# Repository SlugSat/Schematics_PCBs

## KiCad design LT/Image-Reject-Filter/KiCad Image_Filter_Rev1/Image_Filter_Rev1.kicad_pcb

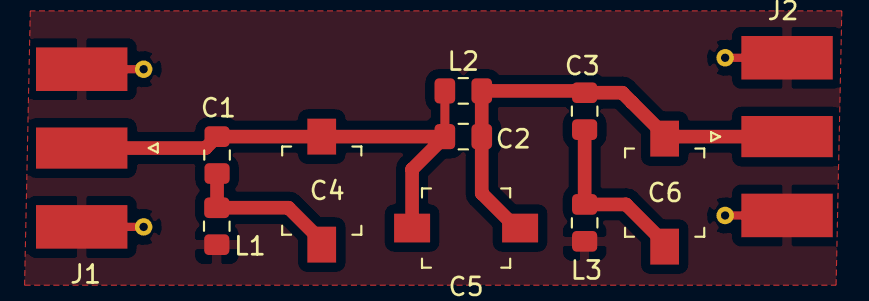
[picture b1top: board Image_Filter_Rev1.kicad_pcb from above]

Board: 2 copper layers, 11 parts (0 on the bottom side), 5 nets.

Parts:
C1, C3: 27pF; C_0805_2012Metric_Pad1.15x1.40mm_HandSolder
C2: 180pF; C_0805_2012Metric_Pad1.15x1.40mm_HandSolder
C4, C5, C6: C_Variable; C_Trimmer_Murata_TZB4-B
J1, J2: Conn_Coaxial; SMA_Molex_73251-1153_EdgeMount_Horizontal
L1, L3: 510nH; L_0805_2012Metric_Pad1.15x1.40mm_HandSolder
L2: 75nH; L_0805_2012Metric_Pad1.15x1.40mm_HandSolder

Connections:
GND: J1.2, J2.2, L1.2, L3.2
unnamed: C1.1, C2.2, C4.1, C5.2, J1.1, L2.1
unnamed: C1.2, C4.2, L1.1
unnamed: C2.1, C3.1, C5.1, C6.1, J2.1, L2.2
unnamed: C3.2, C6.2, L3.1

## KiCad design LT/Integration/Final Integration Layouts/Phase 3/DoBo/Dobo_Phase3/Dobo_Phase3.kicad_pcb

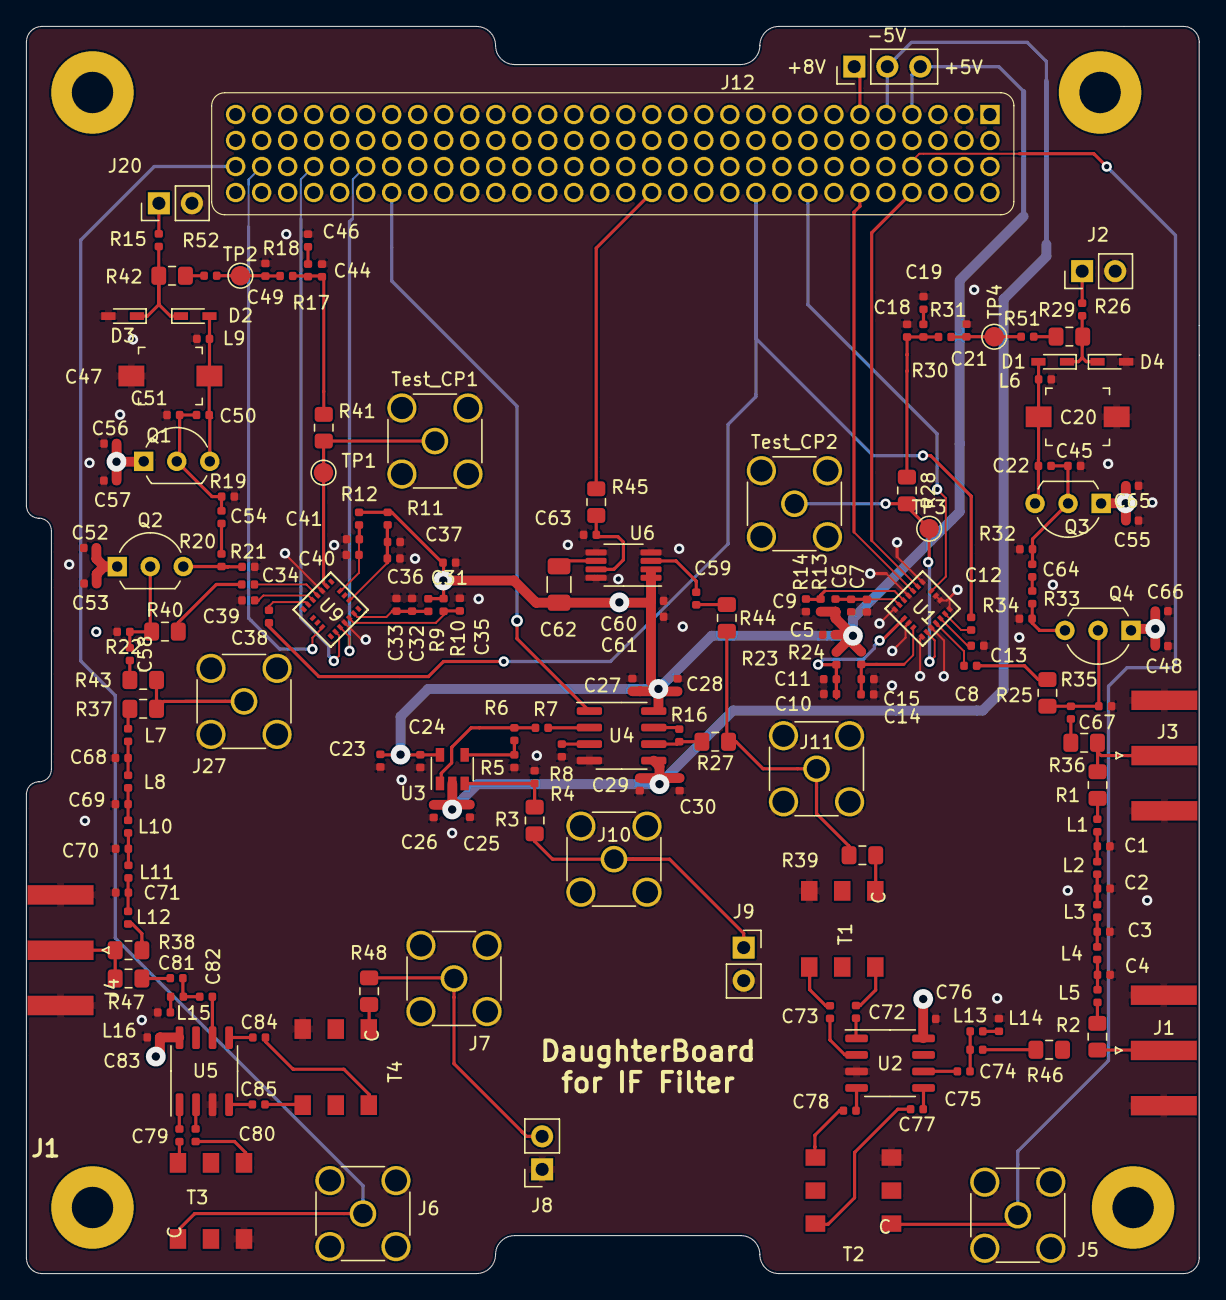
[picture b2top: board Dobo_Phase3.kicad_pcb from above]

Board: 4 copper layers, 90.2 x 95.9 mm, 187 parts (0 on the bottom side), 113 nets.

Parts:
C1: 91pF; C_0402_1005Metric
C2, C3, C4: 160pF; C_0402_1005Metric
C5, C6, C9, C10, C13, C14, C31, C32, C35, C36, C39, C40, C53, C55, C57, C58, C66, C67: 100nF; C_0402_1005Metric
C7, C11, C15, C33, C37, C41, C48, C52, C56, C61, C63, C65: 100pF; C_0402_1005Metric
C8, C12, C34, C38: 1000pF; C_0402_1005Metric
C18, C44: 12nF; C_0402_1005Metric
C19, C46: 80nF; C_0402_1005Metric
C20, C47: SGC35060; C_Trimmer_Murata_TZB4-B
C21, C49: 220nF; C_0402_1005Metric
C22, C50: 22pF; C_0402_1005Metric
C23, C25: 4.7uF; C_0402_1005Metric
C24, C26: 10nF; C_0402_1005Metric
C27, C29, C59, C60: 0.1uH; C_0402_1005Metric
C28, C30: 6.8uH; C_0402_1005Metric
C45, C51: 47pF; C_0402_1005Metric
C54, C64: 10pF; C_0402_1005Metric
C62: 100uH; C_1206_3216Metric
C68, C71: 120pF; C_0402_1005Metric
C69, C70: 200pF; C_0402_1005Metric
C72, C73, C75, C76, C77, C78, C79, C80, C82, C83, C84, C85: 10u; C_0402_1005Metric
C74, C81: 2.2n; C_0402_1005Metric
D1, D2, D3, D4: 1SV304; D_SC-80_HandSoldering
J1, J3, J4: Conn_Coaxial; SMA_Amphenol_132289_EdgeMount
J2, J20: Conn_01x02_Male; PinHeader_1x02_P2.54mm_Vertical
J5, J6, J7, J10, J11, J27: Conn_Coaxial; SMA_Amphenol_132291_Vertical
J8, J9: Conn_01x02_Female; PinSocket_1x02_P2.54mm_Vertical
J12: Conn_01x03_Male; PinHeader_1x03_P2.54mm_Vertical
J46: Bus; STD_PCB_A1_v1.1
L1, L5: shorted; L_0402_1005Metric
L2, L4: 270nH; L_0402_1005Metric
L3: 330nH; L_0402_1005Metric
L6, L9: 680nH; L_0402_1005Metric
L7, L12: Matching; L_0402_1005Metric
L8: 360nH; L_0402_1005Metric
L10: 390pF; L_0402_1005Metric
L11: 360pF; L_0402_1005Metric
L13, L15: 5.6u; L_0402_1005Metric
L14, L16: 680n; L_0402_1005Metric
Q1, Q2, Q3, Q4: 2N5486 JFET; TO-92L_Inline_Wide
R1, R2, R3, R25, R27, R28, R29, R36, R37, R38, R39, R40, R41, R42, R43, R44, R45, R46, R47, R48: 0; R_0805_2012Metric_Pad1.15x1.40mm_HandSolder
R4, R5: 50; R_0402_1005Metric
R6, R16: 1000; R_0402_1005Metric
R7, R8: 29.4; R_0402_1005Metric
R9, R11, R12, R13, R23, R24: 18; R_0402_1005Metric
R10, R14, R15, R26, R51, R52: 10k; R_0402_1005Metric
R17, R30: 62k; R_0402_1005Metric
R18, R19, R22, R31, R32, R35: 1k; R_0402_1005Metric
R20, R33: 1 Ohm; R_0402_1005Metric
R21, R34: 100k; R_0402_1005Metric
T1, T2, T3, T4: Transformer_6; PWB1040L
TP1, TP2, TP3, TP4: TestPoint; TestPoint_Pad_D1.5mm
Test_CP1, Test_CP2: Conn_Coaxial; SMA_Amphenol_132291_Vertical
U1, U9: LMX231X
U2, U5: SA602; SO-8_3.9x4.9mm_P1.27mm
U3: LMH6624; SOT-23-5
U4: LMH6505; SOIC-8_3.9x4.9mm_P1.27mm
U6: AD8361; MSOP-8_3x3mm_P0.65mm

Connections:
+5V: C5.2, C23.1, C24.1, C27.2, C28.2, C31.2, C60.1, C61.1, C62.2, J12.3, J46.4, R9.1, R10.1, R11.1, R12.1, R13.1, R14.1, R23.1, R24.1, U3.5, U4.8, U6.1, U6.2
+8V: C48.2, C52.2, C53.2, C55.2, C56.2, C57.2, C65.2, C66.2, C76.1, C83.1, J12.1, J46.6, Q1.1, Q2.1, Q3.1, Q4.1, U2.8, U5.8
-5V: C25.2, C26.2, C29.2, C30.2, J12.2, J46.5, U3.2, U4.5
/Down_Mixer-IF_Filter: J7.1, J8.2, R48.1
/IF_Filter-VGA: J9.1, J10.1, R3.2
/LPF-Down_Mixer: J4.1, R38.1, R47.2
/Low Pass Filter for 10m PLL/Local_Oscillator_Output: J1.1, R2.1
/PLL_10m_LPF: J3.1, R1.2, R36.1
/PLL_15m-LPF: J27.1, R37.2, R43.1
/VGA-Detector: J11.1, R27.1, R39.2, R44.2
Bus_64: J5.1, J46.64, T2.1
Bus_85: J46.85, U9.13
Bus_87: J46.87, U9.12
Bus_89: J46.89, U9.10
Bus_90: J6.1, J46.90, T3.1
Bus_94: J46.94, U1.12
Bus_96: J46.96, U1.13
Bus_99: J46.98, U1.10
Bus_100: C12.1, C38.1, J46.100
Bus_104: J46.104, R45.1
Bus_114: J46.114, U4.1
CE: C35.2, R10.2, U9.15
CE_2: C9.2, R14.2, U1.15
CPo: R41.2, TP1.1, Test_CP1.1, U9.2
CPo_2: R28.2, TP3.1, Test_CP2.1, U1.2
F_IN: C34.2, U9.4
F_IN_2: C8.2, U1.4
GND: C1.2, C2.2, C3.2, C4.2, C5.1, C6.1, C7.1, C9.1, C10.1, C11.1, C13.1, C14.1, C15.1, C18.1, C19.2, C20.2, C21.2, C23.2, C24.2, C25.1, C26.1, C27.1, C28.1, C29.1, C30.1, C31.1, C32.1, C33.1, C35.1, C36.1, C37.1, C39.1, C40.1, C41.1, C44.1, C45.1, C46.2, C47.2, C48.1, C49.2, C51.1, C52.1, C53.1, C55.1, C56.1, C57.1, C60.2, C61.2, C63.2, C65.1, C66.1, C68.2, C69.2, C70.2, C71.2, C76.2, C83.2, D3.2, D4.2, J1.2, J2.2, J3.2, J4.2, J5.2, J6.2, J7.2, J8.1, J9.2, J10.2, J11.2, J20.2, J27.2, J46.2, L6.2, L9.2, L14.2, L16.2, R4.1, R5.2, R8.2, R19.2, R21.2, R22.2, R32.2, R34.2, R35.2, T1.3, T2.3, T3.3, T4.3, Test_CP1.2, Test_CP2.2, U1.1, U1.3, U1.7, U1.8, U1.9, U1.11, U1.14, U1.17, U1.19, U2.3, U4.4, U5.3, U6.4, U6.5, U6.8, U9.3, U9.14
unnamed: C1.1, L1.2, L2.1
unnamed: C2.1, L2.2, L3.1
unnamed: C3.1, L3.2, L4.1
unnamed: C4.1, L4.2, L5.1
unnamed: C8.1, R25.2
unnamed: C12.2, U1.6
unnamed: C13.2, U1.5
unnamed: C18.2, R28.1, R30.2, R31.2
unnamed: C19.1, R30.1
unnamed: C20.1, C22.2, D1.2, L6.1, Q3.3
unnamed: C21.1, R31.1, R51.1, TP4.1
unnamed: C22.1, C45.2, C64.1, Q3.2, R32.1
unnamed: C34.1, R40.2
unnamed: C38.2, U9.6
unnamed: C39.2, U9.5
unnamed: C44.2, R17.2, R18.2, R41.1
unnamed: C46.1, R17.1
unnamed: C47.1, C50.2, D2.2, L9.1, Q1.3
unnamed: C49.1, R18.1, R52.1, TP2.1
unnamed: C50.1, C51.2, C54.1, Q1.2, R19.1
unnamed: C54.2, R20.2
unnamed: C58.1, Q2.2, R22.1, R40.1
unnamed: C58.2, R43.2
unnamed: C59.1, U6.3
unnamed: C59.2, R44.1
unnamed: C62.1, U6.6
unnamed: C63.1, R45.2, U6.7
unnamed: C64.2, R33.2
unnamed: C67.1, Q4.2, R25.1, R35.1
unnamed: C67.2, R36.2
unnamed: C68.1, L7.2, L8.1
unnamed: C69.1, L8.2, L10.1
unnamed: C70.1, L10.2, L11.1
unnamed: C71.1, L11.2, L12.1
unnamed: C72.1, U2.1
unnamed: C72.2, T1.6
unnamed: C73.1, U2.2
unnamed: C73.2, T1.4
unnamed: C74.1, R46.1
unnamed: C74.2, C75.1, L13.1
unnamed: C75.2, U2.6
unnamed: C77.1, U2.5
unnamed: C77.2, T2.6
unnamed: C78.1, U2.4
unnamed: C78.2, T2.4
unnamed: C79.1, U5.1
unnamed: C79.2, T3.6
unnamed: C80.1, U5.2
unnamed: C80.2, T3.4
unnamed: C81.1, R47.1
unnamed: C81.2, C82.1, L15.1
unnamed: C82.2, U5.6
unnamed: C84.1, U5.5
unnamed: C84.2, T4.6
unnamed: C85.1, U5.4
unnamed: C85.2, T4.4
unnamed: D1.1, D4.1, R26.2, R29.2
unnamed: D2.1, D3.1, R15.2, R42.2
unnamed: J2.1, R26.1
unnamed: J20.1, R15.1
unnamed: L1.1, R1.1
unnamed: L5.2, R2.2
unnamed: L7.1, R37.1
unnamed: L12.2, R38.2
unnamed: L13.2, L14.1
unnamed: L15.2, L16.1
unnamed: Q2.3, R20.1, R21.1
unnamed: Q4.3, R33.1, R34.1
unnamed: R3.1, R4.2, U3.3
unnamed: R5.1, R6.2, U3.4
unnamed: R6.1, R7.2, U3.1
unnamed: R7.1, U4.2
unnamed: R8.1, U4.3
unnamed: R16.1, R27.2, U4.6
unnamed: R16.2, U4.7
unnamed: R29.1, R51.2
unnamed: R39.1, T1.1
unnamed: R42.1, R52.2
unnamed: R48.2, T4.1
V_uC: C32.2, C33.2, R9.2, U9.16
V_uC_2: C6.2, C7.2, R13.2, U1.16
Vcc: C36.2, C37.2, R11.2, U9.18
Vcc_2: C10.2, C11.2, R23.2, U1.18
Vp: C40.2, C41.2, R12.2, U9.20
Vp_2: C14.2, C15.2, R24.2, U1.20

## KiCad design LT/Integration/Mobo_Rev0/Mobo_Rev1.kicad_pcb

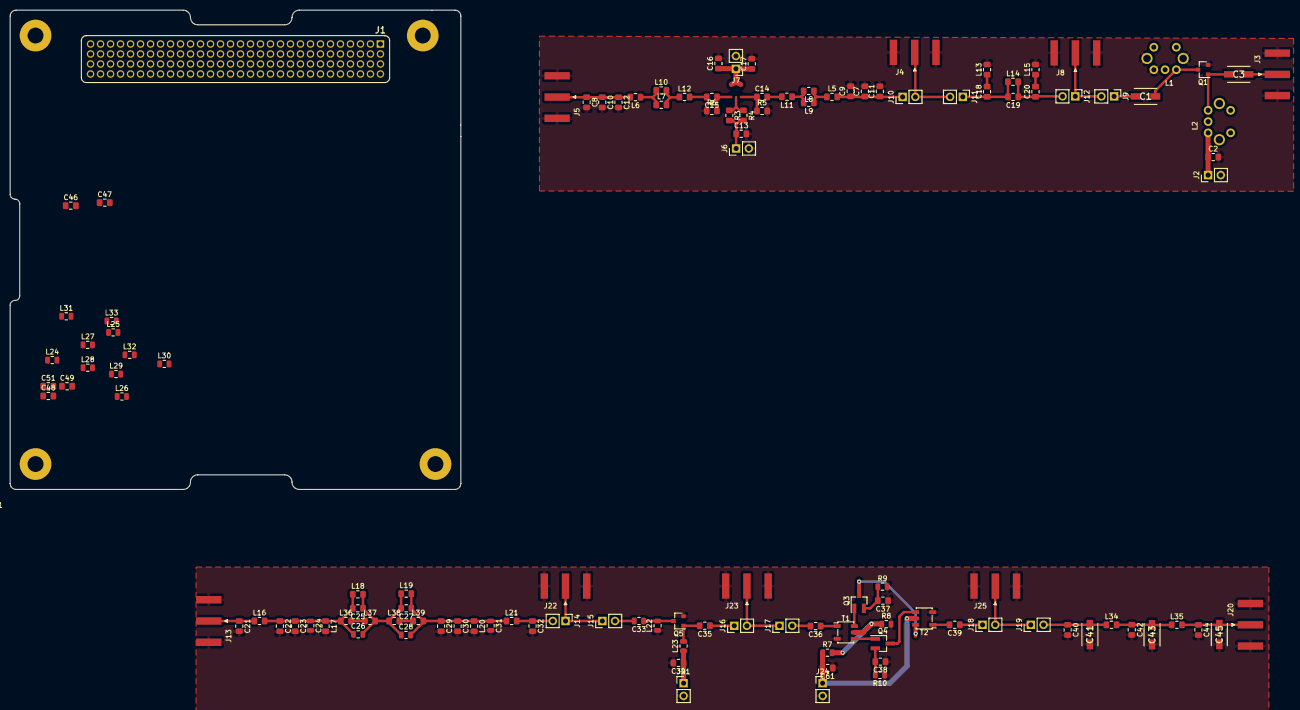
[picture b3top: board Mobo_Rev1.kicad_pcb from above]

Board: 2 copper layers, 90.2 x 95.9 mm, 124 parts (0 on the bottom side), 54 nets.

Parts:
C1, C3: 8-30pF; CAP_trimmer_SGC3_Download
C2, C34: 1uF; C_0805_2012Metric_Pad1.15x1.40mm_HandSolder
C7, C8: 220pF; C_0805_2012Metric_Pad1.15x1.40mm_HandSolder
C9, C10: 22pF; C_0805_2012Metric_Pad1.15x1.40mm_HandSolder
C11, C12: 330pF; C_0805_2012Metric_Pad1.15x1.40mm_HandSolder
C13: 10nH; C_0805_2012Metric_Pad1.15x1.40mm_HandSolder
C14, C15, C16, C17: 10nF; C_0805_2012Metric_Pad1.15x1.40mm_HandSolder
C18, C20: 27pF; C_0805_2012Metric_Pad1.15x1.40mm_HandSolder
C19: 180pF; C_0805_2012Metric_Pad1.15x1.40mm_HandSolder
C21, C32: No Connect; C_0805_2012Metric_Pad1.15x1.40mm_HandSolder
C22: 560p; C_0805_2012Metric_Pad1.15x1.40mm_HandSolder
C23, C30: 56pF; C_0805_2012Metric_Pad1.15x1.40mm_HandSolder
C24, C26, C28, C31: No Connect; C_0805_2012Metric
C25: 18pF; C_0805_2012Metric_Pad1.15x1.40mm_HandSolder
C27: 43pF; C_0805_2012Metric_Pad1.15x1.40mm_HandSolder
C29: 560pF; C_0805_2012Metric_Pad1.15x1.40mm_HandSolder
C33: C_Variable; C_0805_2012Metric
C35, C36, C39, C46, C47, C48, C49, C51: C; C_0805_2012Metric_Pad1.15x1.40mm_HandSolder
C37, C38, C61: 100n; C_0805_2012Metric_Pad1.15x1.40mm_HandSolder
C40, C44: 180p; C_0805_2012Metric_Pad1.15x1.40mm_HandSolder
C41, C43, C45: C_Variable; CAP_trimmer_SGC3_Download
C42: 270p; C_0805_2012Metric_Pad1.15x1.40mm_HandSolder
J1: Bus; STD_PCB_A1_v1.1
J2, J6, J7, J9, J10, J11, J12, J14, J15, J16, J17, J18, J19, J21, J24: Conn_01x02_Male; PinHeader_1x02_P2.54mm_Vertical
J3, J4, J5, J8, J13, J20: Conn_Coaxial; SMA_Amphenol_132289_EdgeMount
J22, J23, J25: Conn_01x02_Male; SMA_Amphenol_132289_EdgeMount
L1: 0.54-0.81uH; IND_trimmer_7M3
L2: 1.8-2.6uH; IND_trimmer_7M3
L5, L6: 3.9nH; L_0805_2012Metric_Pad1.15x1.40mm_HandSolder
L7, L8, L9, L10, L17, L20: 47nH; L_0805_2012Metric_Pad1.15x1.40mm_HandSolder
L11, L12: 150nH; L_0805_2012Metric_Pad1.15x1.40mm_HandSolder
L13, L15: 470nH; L_0805_2012Metric_Pad1.15x1.40mm_HandSolder
L14: 82nH; L_0805_2012Metric_Pad1.15x1.40mm_HandSolder
L16, L21: Shorted Connection; L_0805_2012Metric_Pad1.15x1.40mm_HandSolder
L18, L19: No Connect; L_0805_2012Metric_Pad1.15x1.40mm_HandSolder
L22: LTRIM; L_0805_2012Metric
L23: 1.8-2.6uH; L_0805_2012Metric
L24, L25, L26, L27, L28, L29, L30, L31, L32, L33: L; L_0805_2012Metric
L34, L35: 330n; L_0805_2012Metric_Pad1.15x1.40mm_HandSolder
L36: 680nH; L_0805_2012Metric_Pad1.15x1.40mm_HandSolder
L37: 6.8nH; L_0805_2012Metric_Pad1.15x1.40mm_HandSolder
L38: 1.5uH; L_0805_2012Metric_Pad1.15x1.40mm_HandSolder
L39: 72nH; L_0805_2012Metric_Pad1.15x1.40mm_HandSolder
Q1: 2N5486; SOT-23
Q3: Q_NPN_BEC; SOT-23_Handsoldering
Q4: Q_PNP_BEC; SOT-23_Handsoldering
Q5: Q_NJFET_DSG; SOT-23
R3, R4: 120; R_0805_2012Metric_Pad1.15x1.40mm_HandSolder
R5, R6: 330; R_0805_2012Metric_Pad1.15x1.40mm_HandSolder
R7: 33k; C_0805_2012Metric
R8: 47k; C_0805_2012Metric
R9, R10: 470; C_0805_2012Metric
T1, T2: TC2-1T+; Transformer_MACOM_SM-22

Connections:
+5V: C16.1, C17.1, J7.1
+8V: C2.1, C34.1, J2.1, J21.1, L2.1, L23.1
/29.4 MHz Bandpass Filter/29.4BPF_OUT: J14.1, J22.1
/Image Reject Filter/Image_Reject_Out: J8.1, J12.1
/LNA/LNAout: C3.1, J3.1
/Power Amplifier/PA_OUT: J18.2, J25.1
/Pre Amplifier/PREAMP_OUT: J16.2, J23.1
/Variable Attenuator/Variable_Attenuator_Out: J4.1, J10.2
GND: C2.2, C7.2, C8.2, C9.2, C10.2, C11.2, C12.2, C13.2, C16.2, C17.2, C21.2, C22.2, C23.2, C24.2, C29.2, C30.2, C31.2, C32.2, C34.2, C37.1, C38.1, C40.2, C41.2, C42.2, C43.2, C44.2, C45.2, C61.1, J2.2, J3.2, J4.2, J5.2, J6.2, J7.2, J8.2, J13.2, J20.2, J21.2, J22.2, J23.2, J24.2, J25.2, L1.2, L13.2, L15.2, L17.2, L20.2, L22.1, Q1.3, Q5.2, R5.2, R6.1, R8.2, R9.2, R10.1, T1.2, T2.2
unnamed: C1.1, L1.1, Q1.2
unnamed: C1.2, J9.1
unnamed: C3.2, L2.2, Q1.1
unnamed: C8.1, C10.1, C12.1, J5.1, L6.2
unnamed: C7.1, C9.1, C11.1, J10.1, L5.2
unnamed: C13.1, J6.1, R3.2, R4.2
unnamed: C14.1, R5.1
unnamed: C14.2, L11.2
unnamed: C15.1, R6.2
unnamed: C15.2, L12.2
unnamed: C18.1, C19.2, J11.1, L14.1
unnamed: C18.2, L13.1
unnamed: C19.1, C20.1, J12.2, L14.2
unnamed: C20.2, L15.1
unnamed: C21.1, J13.1, L16.1
unnamed: C22.1, C23.1, C24.1, C25.2, C26.1, L16.2, L17.1, L18.1, L36.1
unnamed: C25.1, C26.2, C27.2, C28.1, L18.2, L19.1, L37.2, L38.1
unnamed: C27.1, C28.2, C29.1, C30.1, C31.1, L19.2, L20.1, L21.1, L39.2
unnamed: C32.1, J14.2, L21.2
unnamed: C33.1, L22.2, Q5.3
unnamed: C33.2, J15.2
unnamed: C35.1, J16.1
unnamed: C35.2, L23.2, Q5.1
unnamed: C36.1, T1.1
unnamed: C36.2, J17.2
unnamed: C37.2, Q3.2, R9.1
unnamed: C38.2, Q4.2, R10.2
unnamed: C39.1, J18.1
unnamed: C39.2, T2.1
unnamed: C40.1, C41.1, J19.2, L34.1
unnamed: C42.1, C43.1, L34.2, L35.1
unnamed: C44.1, C45.1, J20.1, L35.2
unnamed: C61.2, J24.1, R7.1, T2.4
unnamed: L5.1, L8.1, L9.1
unnamed: L6.1, L7.1, L10.1
unnamed: L7.2, L10.2, L12.1
unnamed: L8.2, L9.2, L11.1
unnamed: L36.2, L37.1
unnamed: L38.2, L39.1
unnamed: Q3.1, T1.5
unnamed: Q3.3, T2.5
unnamed: Q4.1, T1.3
unnamed: Q4.3, T2.3
unnamed: R3.1, R4.1
unnamed: R7.2, R8.1, T1.4

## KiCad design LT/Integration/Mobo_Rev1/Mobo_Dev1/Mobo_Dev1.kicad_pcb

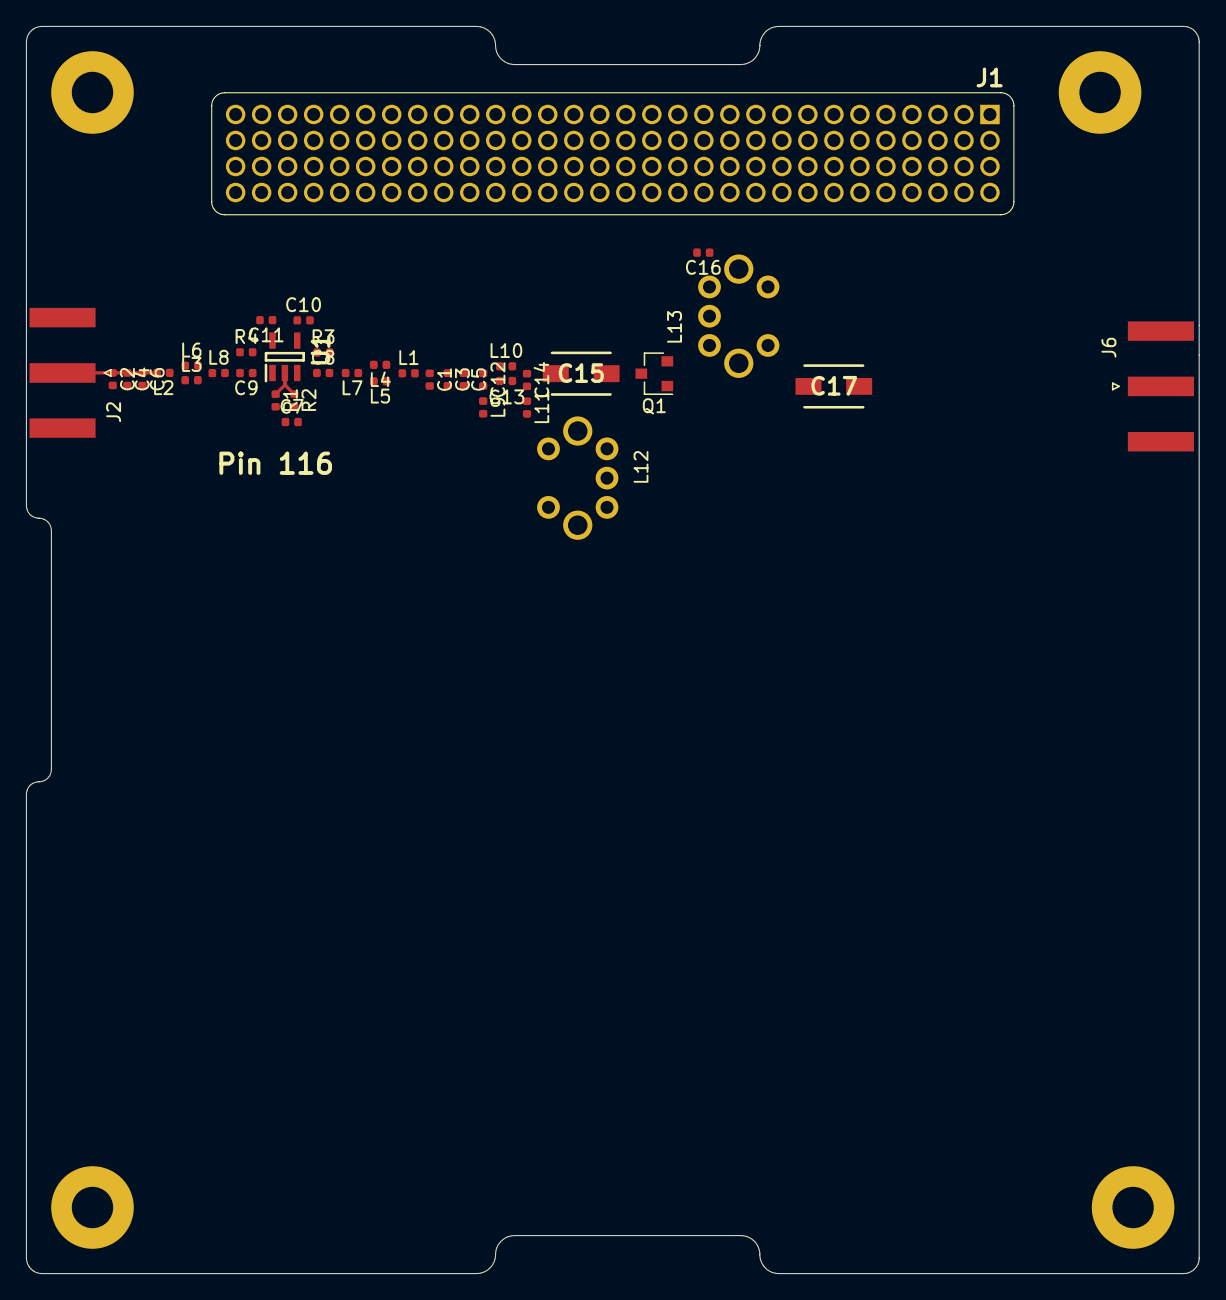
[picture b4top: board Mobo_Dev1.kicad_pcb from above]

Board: 4 copper layers, 90.2 x 95.9 mm, 39 parts (0 on the bottom side), 22 nets.

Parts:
C1, C2: 220pF; C_0402_1005Metric
C3, C4: 22pF; C_0402_1005Metric
C5, C6: 330pF; C_0402_1005Metric
C7: 10nH; C_0402_1005Metric
C8, C9, C10, C11: 10nF; C_0402_1005Metric
C12, C14: 27pF; C_0402_1005Metric
C13: 180pF; C_0402_1005Metric
C15, C17: 8-30pF; CAP_trimmer_SGC3_Download
C16: 1uF; C_0402_1005Metric
J1: Bus; STD_PCB_A1_v1.1
J2, J6: Conn_Coaxial; SMA_Amphenol_132289_EdgeMount
L1, L2: 3.9nH; L_0402_1005Metric
L3, L4, L5, L6: 47nH; L_0402_1005Metric
L7, L8: 150nH; L_0402_1005Metric
L9, L11: 470nH; L_0402_1005Metric
L10: 82nH; L_0402_1005Metric
L12: 0.54-0.81uH; IND_trimmer_7M3
L13: 1.8-2.6uH; IND_trimmer_7M3
Q1: 2N5486; SOT-23
R1, R2: 120; R_0402_1005Metric
R3, R4: 330; R_0402_1005Metric
U1: BAP64Q

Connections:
+5V: C10.1, C11.1, U1.4, U1.5
+8V: C16.1, L13.3
/Image Reject Filter/Image_Reject_Out: C13.1, C14.1, L10.2
/Image Reject Filter/Variable_Attenuator_Out: C12.1, C13.2, L10.1
/Low Noise Amplifier/LNAout: C17.1, J6.1
/Variable Attenuator/Control_Voltage_From_MicroController: C7.1, R1.2, R2.2
/Variable Attenuator/Variable_Attenuator_Out: C1.1, C3.1, C5.1, L1.2
GND: C1.2, C2.2, C3.2, C4.2, C5.2, C6.2, C7.2, C10.2, C11.2, C16.2, J2.2, J6.2, L9.2, L11.2, L12.2, L12.3, Q1.2, R3.2, R4.1
unnamed: C2.1, C4.1, C6.1, J2.1, L2.2
unnamed: C8.1, R3.1, U1.3
unnamed: C8.2, L7.2
unnamed: C9.1, R4.2, U1.1
unnamed: C9.2, L8.2
unnamed: C12.2, L9.1
unnamed: C14.2, L11.1
unnamed: C15.1, L12.1, Q1.3
unnamed: C17.2, L13.1, L13.2, Q1.1
unnamed: L1.1, L4.1, L5.1
unnamed: L2.1, L3.1, L6.1
unnamed: L3.2, L6.2, L8.1
unnamed: L4.2, L5.2, L7.1
unnamed: R1.1, R2.1, U1.2

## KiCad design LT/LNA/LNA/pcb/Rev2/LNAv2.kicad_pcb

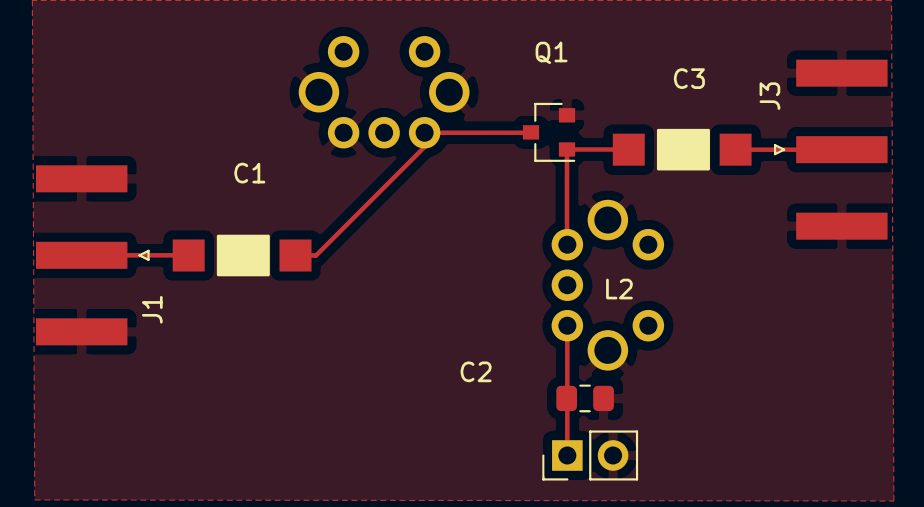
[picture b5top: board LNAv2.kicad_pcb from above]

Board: 2 copper layers, 9 parts (0 on the bottom side), 6 nets.

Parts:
C1, C3: 8-30pF; Variable Capacitor
C2: 1uF; C_0805_2012Metric_Pad1.15x1.40mm_HandSolder
J1, J3: Conn_Coaxial; SMA_Amphenol_132289_EdgeMount
J2: Conn_01x02_Male; PinHeader_1x02_P2.54mm_Vertical
L1: 0.54-0.81uH; IND_trimmer_7M3
L2: 1.8-2.6uH; IND_trimmer_7M3
Q1: 2N5486; SOT-23

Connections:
+8V: C2.1, J2.1, L2.1
GND: C2.2, J1.2, J2.2, J3.2, L1.3, L1.5, L2.5, Q1.2
unnamed: C1.1, L1.1, Q1.3
unnamed: C1.2, J1.1
unnamed: C3.1, J3.1
unnamed: C3.2, L2.3, Q1.1

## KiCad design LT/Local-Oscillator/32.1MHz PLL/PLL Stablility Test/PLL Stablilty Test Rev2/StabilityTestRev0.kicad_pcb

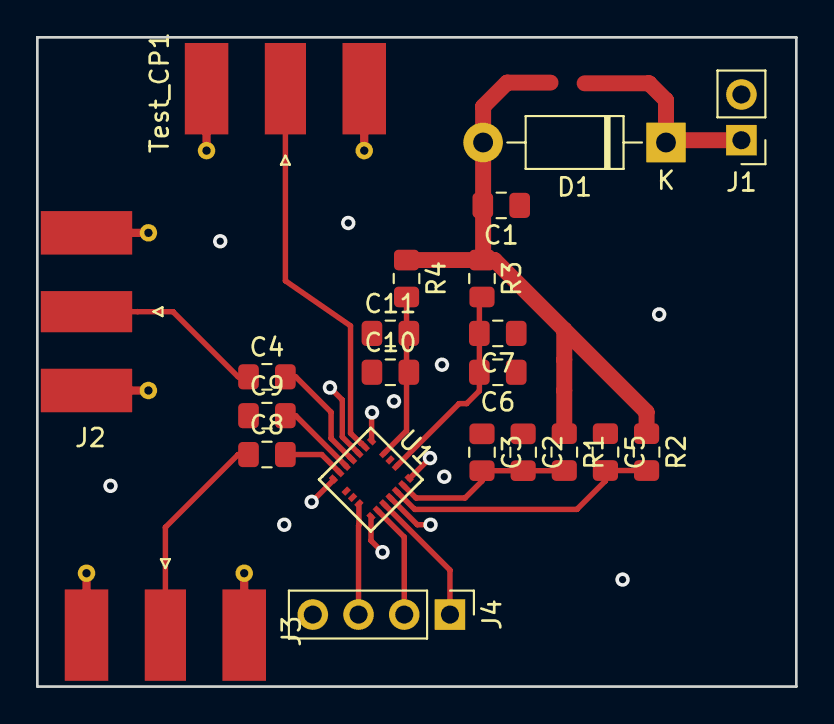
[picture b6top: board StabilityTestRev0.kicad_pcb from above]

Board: 2 copper layers, 42.2 x 36.1 mm, 22 parts (0 on the bottom side), 16 nets.

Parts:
C1: C; C_0805_2012Metric_Pad1.15x1.40mm_HandSolder
C2, C5, C6, C9, C10: 100nF; C_0805_2012Metric_Pad1.15x1.40mm_HandSolder
C3, C7, C11: 100pF; C_0805_2012Metric_Pad1.15x1.40mm_HandSolder
C4, C8: 1000pF; C_0805_2012Metric_Pad1.15x1.40mm_HandSolder
D1: DIODE; D_DO-41_SOD81_P10.16mm_Horizontal
J1: Conn_01x02_Male; PinHeader_1x02_P2.54mm_Vertical
J2, J3: Conn_Coaxial; SMA_Molex_73251-1153_EdgeMount_Horizontal
J4: Conn_01x04_Male; PinHeader_1x04_P2.54mm_Vertical
R1, R3, R4: 18; R_0805_2012Metric_Pad1.15x1.40mm_HandSolder
R2: 10k; R_0805_2012Metric_Pad1.15x1.40mm_HandSolder
Test_CP1: Conn_Coaxial; SMA_Molex_73251-1153_EdgeMount_Horizontal
U1: LMX231X

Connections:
/PD/CE: C5.2, R2.2, U1.15
/PD/Clock: J4.3, U1.10
/PD/Data: J4.2, U1.12
/PD/F_IN: C4.2, U1.4
/PD/LE: J4.1, U1.13
/PD/OSC_IN: C8.2, U1.6
/PD/PLL+Power: C1.2, D1.2, R1.1, R2.1, R3.1, R4.1
/PD/V_uC: C2.2, C3.2, R1.2, U1.16
/PD/Vcc: C6.2, C7.2, R3.2, U1.18
/PD/Vp: C10.2, C11.2, R4.2, U1.20
CPo: Test_CP1.1, U1.2
GND: C1.1, C2.1, C3.1, C5.1, C6.1, C7.1, C9.1, C10.1, C11.1, J1.2, J2.2, J3.2, J4.4, Test_CP1.2, U1.3, U1.14
unnamed: C8.1, J3.1
unnamed: C9.2, U1.5
unnamed: D1.1, J1.1
VCO_OUT: C4.1, J2.1
